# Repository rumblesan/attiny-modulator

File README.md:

# Attiny85 Modulator

## Description

Based on the [JNTUB](https://github.com/joyfulnoisesynth/JNTUB) designed by Ben Reeves

## Contact

Drop me an email at guy@rumblesan.com

## License

BSD License.

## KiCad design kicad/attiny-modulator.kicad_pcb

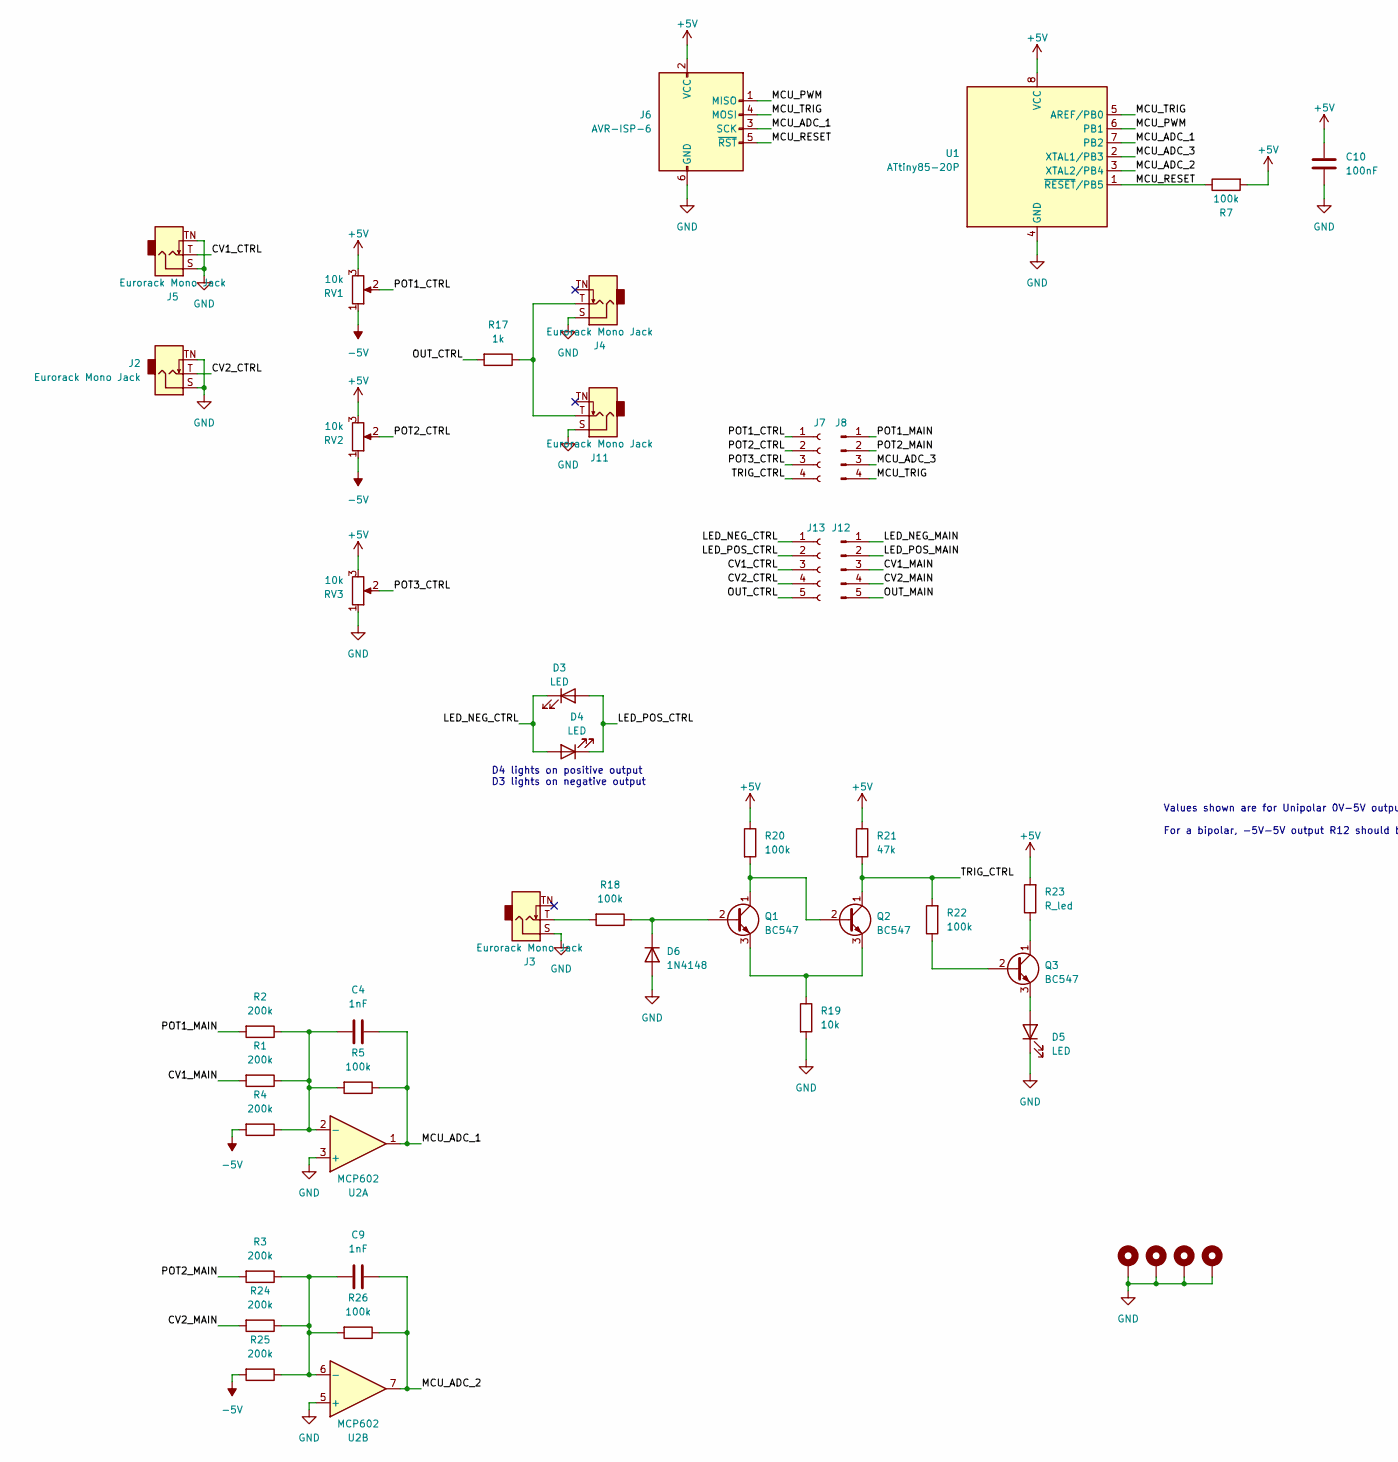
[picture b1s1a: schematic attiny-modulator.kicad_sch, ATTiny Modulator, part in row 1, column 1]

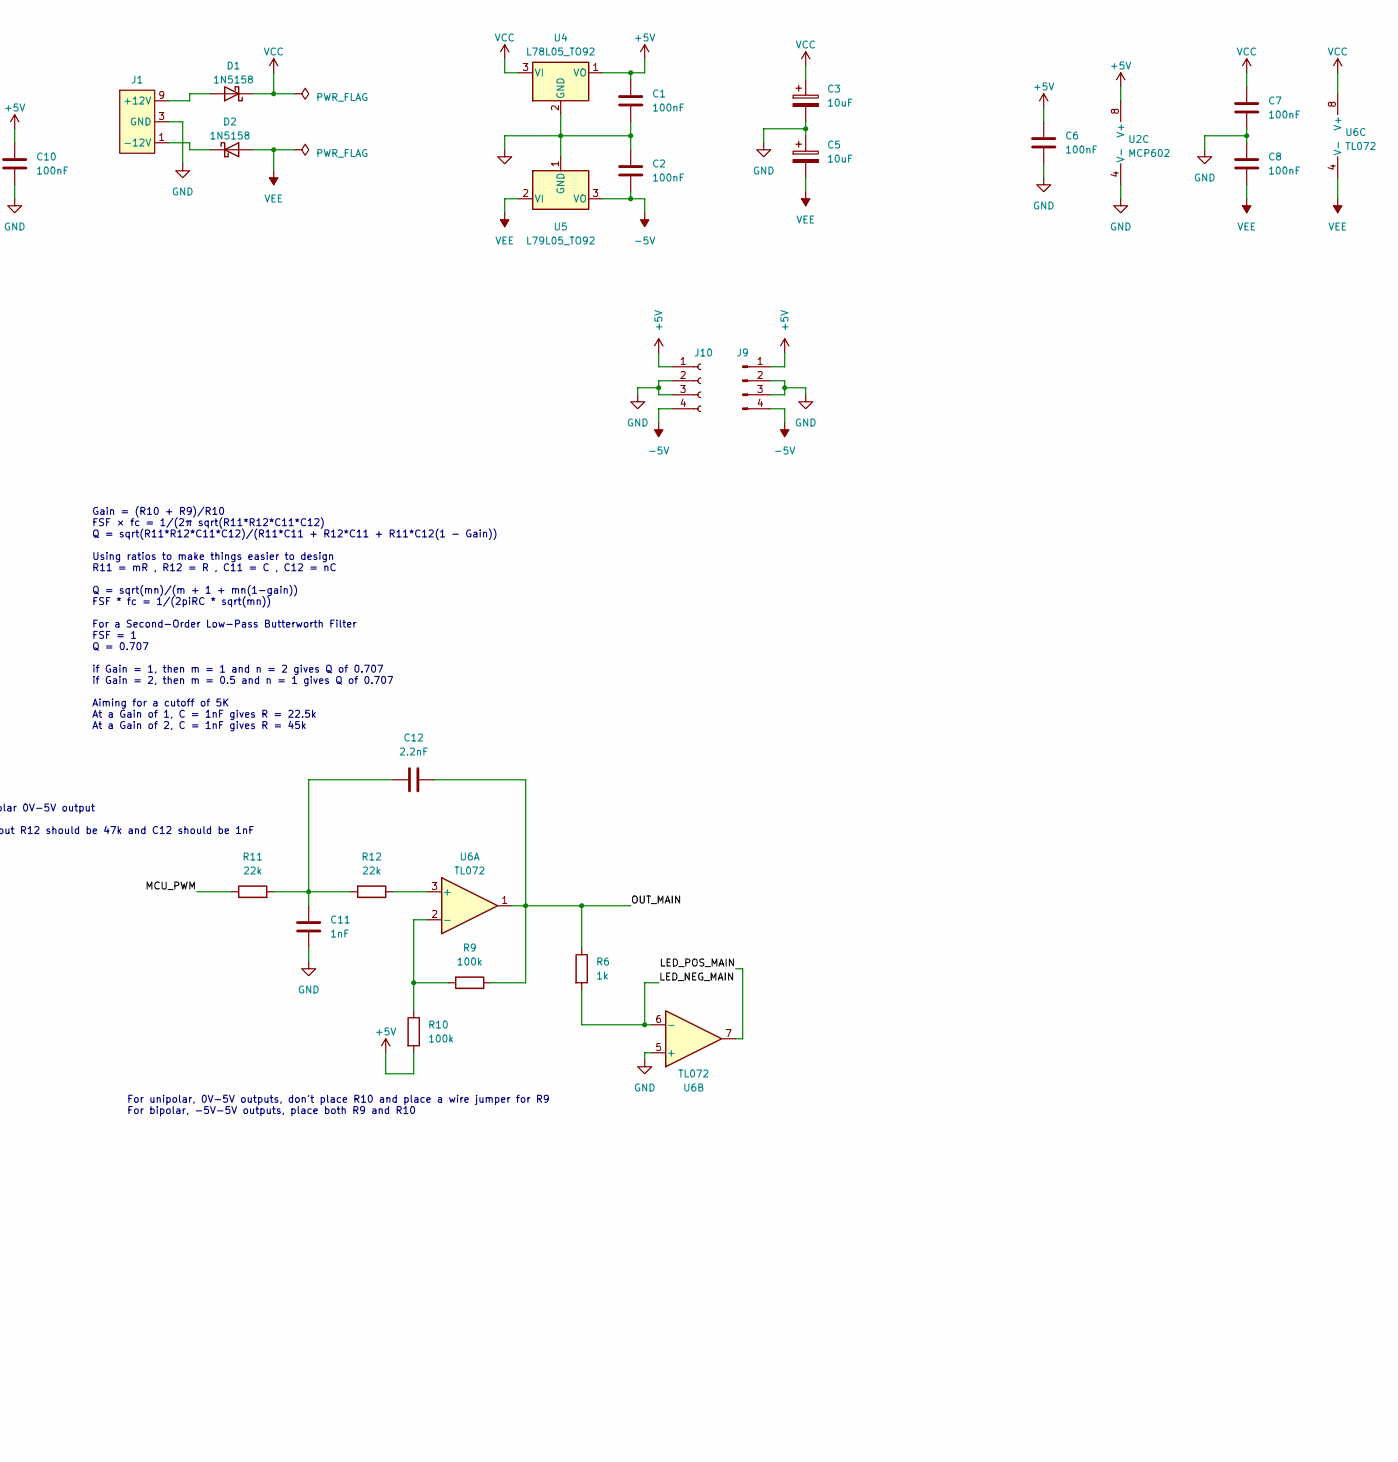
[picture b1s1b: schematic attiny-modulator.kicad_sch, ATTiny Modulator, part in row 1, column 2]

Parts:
C1, C2, C6, C7, C8, C10: 100nF; C_Rect_L7.0mm_W2.5mm_P5.00mm; Tolerance 5%
C3, C5: 10uF; CP_Radial_D5.0mm_P2.00mm; Tolerance 20%; Voltage 50v
C4, C9, C11: 1nF; C_Rect_L7.0mm_W2.5mm_P5.00mm; Tolerance 5%
C12: 2.2nF; C_Rect_L7.0mm_W2.5mm_P5.00mm; Tolerance 5%
D1, D2: 1N5158; D_DO-41_SOD81_P10.16mm_Horizontal
D3, D4, D5: LED; LED_D1.8mm_W3.3mm_H2.4mm
D6: 1N4148; D_DO-35_SOD27_P7.62mm_Horizontal
H1, H2, H3, H4: MountingHole_Pad; MountingHole_3.2mm_M3_DIN965_Pad
J1: Eurorack Power Small; Eurorack_PowerHeader_2x05_P2.54mm_Shrouded
J2, J3, J4, J5, J11: Eurorack Mono Jack; Jack_3.5mm_QingPu_WQP-PJ398SM_Vertical; mpn WQP-WQP518MA
J6: AVR-ISP-6; PinHeader_2x03_P2.54mm_Vertical
J7, J10: Conn_01x04_Socket; PinSocket_1x04_P2.54mm_Vertical
J8, J9: Conn_01x04_Pin; PinHeader_1x04_P2.54mm_Vertical
J12: Conn_01x05_Pin; PinHeader_1x05_P2.54mm_Vertical
J13: Conn_01x05_Socket; PinSocket_1x05_P2.54mm_Vertical
Q1, Q2, Q3: BC547; TO-92_Inline_Wide
R1, R2, R3, R4, R24, R25: 200k; R_Axial_DIN0207_L6.3mm_D2.5mm_P10.16mm_Horizontal; Tolerance 1%
R5, R7, R9, R10, R18, R20, R22, R26: 100k; R_Axial_DIN0207_L6.3mm_D2.5mm_P10.16mm_Horizontal; Tolerance 1%
R6, R17: 1k; R_Axial_DIN0207_L6.3mm_D2.5mm_P10.16mm_Horizontal; Tolerance 1%
R11, R12: 22k; R_Axial_DIN0207_L6.3mm_D2.5mm_P10.16mm_Horizontal; Tolerance 1%
R19: 10k; R_Axial_DIN0207_L6.3mm_D2.5mm_P10.16mm_Horizontal; Tolerance 1%
R21: 47k; R_Axial_DIN0207_L6.3mm_D2.5mm_P10.16mm_Horizontal; Tolerance 1%
R23: R_led; R_Axial_DIN0207_L6.3mm_D2.5mm_P10.16mm_Horizontal; Tolerance 1%
RV1, RV2, RV3: 10k; Potentiometer_Alpha_RD901F-40-00D_Single_Vertical
U1: ATtiny85-20P; DIP-8_W7.62mm_Socket
U2: MCP602; DIP-8_W7.62mm_Socket
U4: L78L05_TO92; TO-92_Inline_Wide
U5: L79L05_TO92; TO-92_Inline_Wide
U6: TL072; DIP-8_W7.62mm_Socket

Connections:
+5V: C1.1, C6.1, C10.1, J6.2 (VCC), J9.1, J10.1, R7.2, R10.2, R20.1, R21.1, R23.2, RV1.3, RV2.3, RV3.3, U1.8 (VCC), U2.8 (V+), U4.1 (VO)
-5V: C2.2, J9.4, J10.4, R4.2, R25.2, RV1.1, RV2.1, U5.3 (VO)
/CV1_CTRL: J5.T, J13.3
/CV1_MAIN: J12.3, R1.2
/CV2_CTRL: J2.T, J13.4
/CV2_MAIN: J12.4, R24.2
/LED_NEG_CTRL: D3.1 (K), D4.2 (A), J13.1
/LED_NEG_MAIN: J12.1, R6.2, U6.6 (-)
/LED_POS_CTRL: D3.2 (A), D4.1 (K), J13.2
/LED_POS_MAIN: J12.2, U6.7
/MCU_ADC_1: C4.2, J6.3 (SCK), R5.1, U1.7 (PB2), U2.1
/MCU_ADC_2: C9.2, R26.1, U1.3 (XTAL2/PB4), U2.7
/MCU_ADC_3: J8.3, U1.2 (XTAL1/PB3)
/MCU_PWM: J6.1 (MISO), R11.1, U1.6 (PB1)
/MCU_RESET: J6.5 (~RST), R7.1, U1.1 (~RESET/PB5)
/MCU_TRIG: J6.4 (MOSI), J8.4, U1.5 (AREF/PB0)
/OUT_CTRL: J13.5, R17.2
/OUT_MAIN: C12.1, J12.5, R6.1, R9.1, U6.1
/POT1_CTRL: J7.1, RV1.2
/POT1_MAIN: J8.1, R2.2
/POT2_CTRL: J7.2, RV2.2
/POT2_MAIN: J8.2, R3.2
/POT3_CTRL: J7.3, RV3.2
/TRIG_CTRL: J7.4, Q2.1 (C), R21.2, R22.2
GND: C1.2, C2.1, C3.2, C5.1, C6.2, C7.2, C8.1, C10.2, C11.1, D5.1 (K), D6.2 (A), H1.1, H2.1, H3.1, H4.1, J1.3 (GND), J1.4 (GND), J1.5 (GND), J1.6 (GND), J1.7 (GND), J1.8 (GND), J2.S, J2.TN, J3.S, J4.S, J5.S, J5.TN, J6.6 (GND), J9.2, J9.3, J10.2, J10.3, J11.S, R19.2, RV3.1, U1.4 (GND), U2.3 (+), U2.4 (V-), U2.5 (+), U4.2 (GND), U5.1 (GND), U6.5 (+)
unnamed: C11.2, C12.2, R11.2, R12.2
unnamed: D1.2 (A), J1.9 (+12V), J1.10 (+12V)
unnamed: D2.1 (K), J1.1 (-12V), J1.2 (-12V)
unnamed: D5.2 (A), Q3.3 (E)
unnamed: D6.1 (K), Q1.2 (B), R18.1
unnamed: J3.T, R18.2
unnamed: J4.T, J11.T, R17.1
unnamed: Q1.1 (C), Q2.2 (B), R20.2
unnamed: Q1.3 (E), Q2.3 (E), R19.1
unnamed: Q3.2 (B), R22.1
unnamed: Q3.1 (C), R23.1
unnamed: C4.1, R1.1, R2.1, R4.1, R5.2, U2.2 (-)
unnamed: C9.1, R3.1, R24.1, R25.1, R26.2, U2.6 (-)
unnamed: R12.1, U6.3 (+)
unnamed: R9.2, R10.1, U6.2 (-)
VCC: C3.1, C7.1, D1.1 (K), U4.3 (VI), U6.8 (V+)
VEE: C5.2, C8.2, D2.2 (A), U5.2 (VI), U6.4 (V-)

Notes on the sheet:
D4 lights on positive output D3 lights on negative output
For unipolar, 0V-5V outputs, don't place R10 and place a wire jumper for R9 For bipolar, -5V-5V outputs, place both R9 and R10
Gain = (R10 + R9)/R10 FSF × fc = 1/(2π sqrt(R11*R12*C11*C12) Q = sqrt(R11*R12*C11*C12)/(R11*C11 + R12*C11 + R11*C12(1 − Gain)) Using ratios to make things easier to design R11 = mR , R12 = R , C11 = C , C12 = nC Q = sqrt(mn)/(m + 1 + mn(1-gain)) FSF * fc = 1/(2piRC * sqrt(mn)) For a Second-Order Lo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
Values shown are for Unipolar 0V-5V output For a bipolar, -5V-5V output R12 should be 47k and C12 should be 1nF

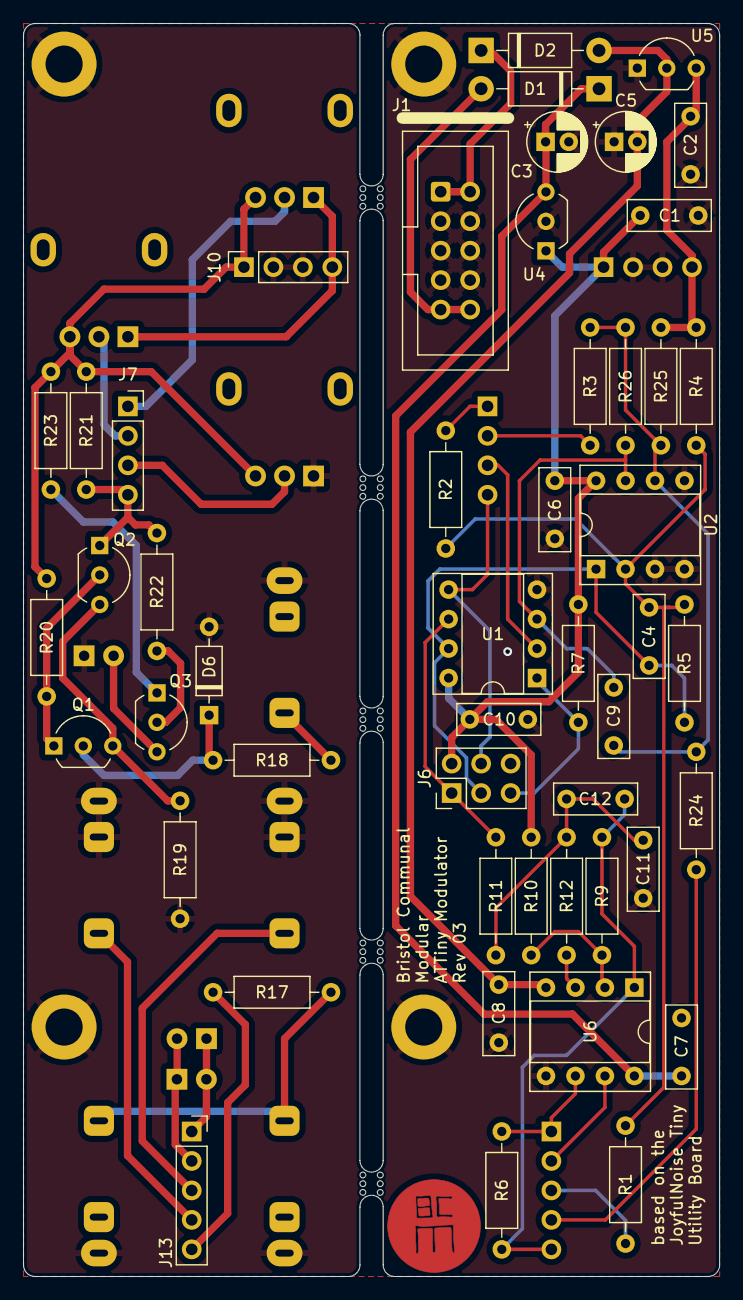
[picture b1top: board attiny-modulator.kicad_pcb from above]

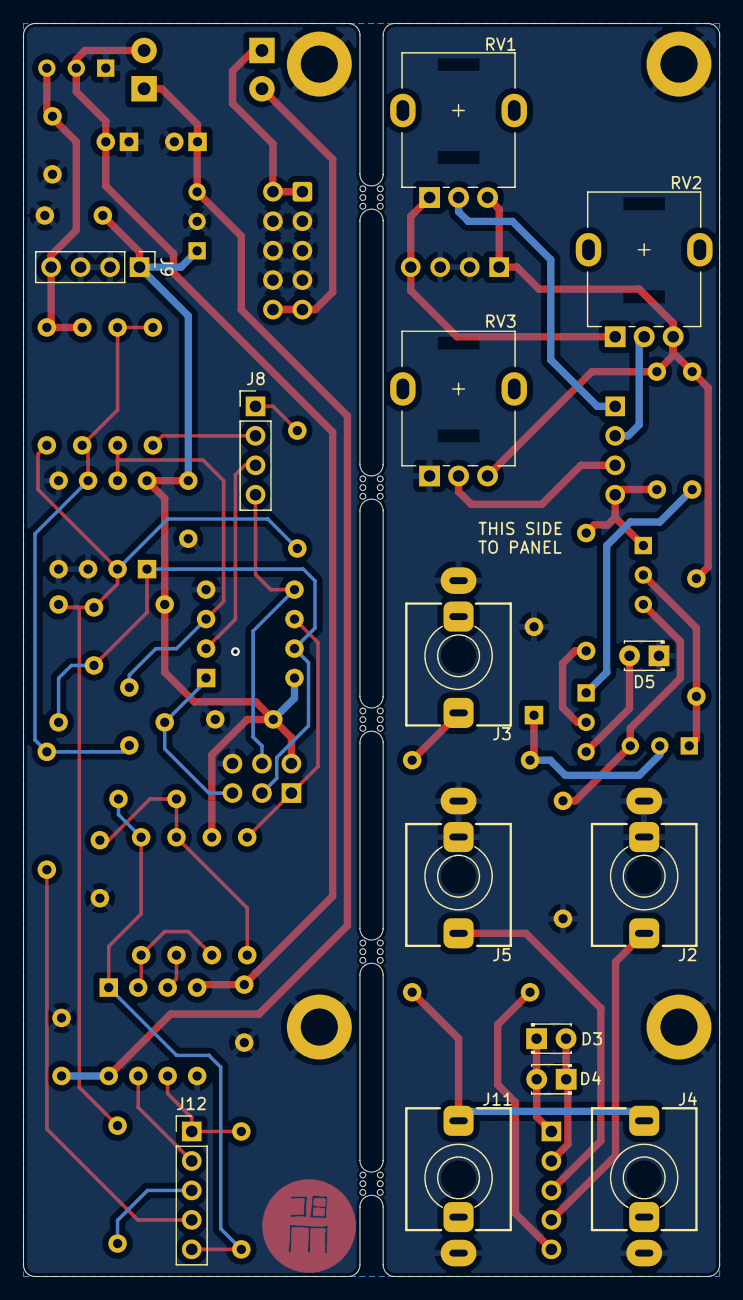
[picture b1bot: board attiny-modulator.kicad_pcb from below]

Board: 2 copper layers, 60.0 x 108.0 mm, 72 parts (14 on the bottom side), 42 nets.

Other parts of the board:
mouse-bite-2mm-slot, mouse-bite-2mm-slot#2, mouse-bite-2mm-slot#3, mouse-bite-2mm-slot#4, mouse-bite-2mm-slot#5: VAL**; mouse-bite-2mm-slot

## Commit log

2023-05-21 Creating kicad project
2023-05-21 initial commit with a working firmware file
2023-06-19 Updating schematic, layout and front panel
2023-06-19 Update readme with link to JNUTB repo
2023-07-06 Fixing bugs with circuit
2023-07-06 Updating basics of firmware
2023-12-17 getting envelope things working kindof
2023-12-17 Getting envelope curves working
2023-12-24 Getting envelope finally working
2023-12-24 ignore datasheet directory
2023-12-24 Add build directory
2023-12-24 Tweaks for rev02
2023-12-24 Adding rev02 gerbers
2024-07-06 Refreshing board layout
2024-09-16 Starting to add lfo firmware

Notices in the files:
kicad/attiny-modulator.kicad_pcb:
creativecommons.org/licenses/by/4.0
License: CC BY 4.0
